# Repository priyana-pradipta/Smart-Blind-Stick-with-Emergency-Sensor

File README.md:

# Smart-Blind-Stick-with-Emergency-Sensor
Embedded Systems Course Final Project

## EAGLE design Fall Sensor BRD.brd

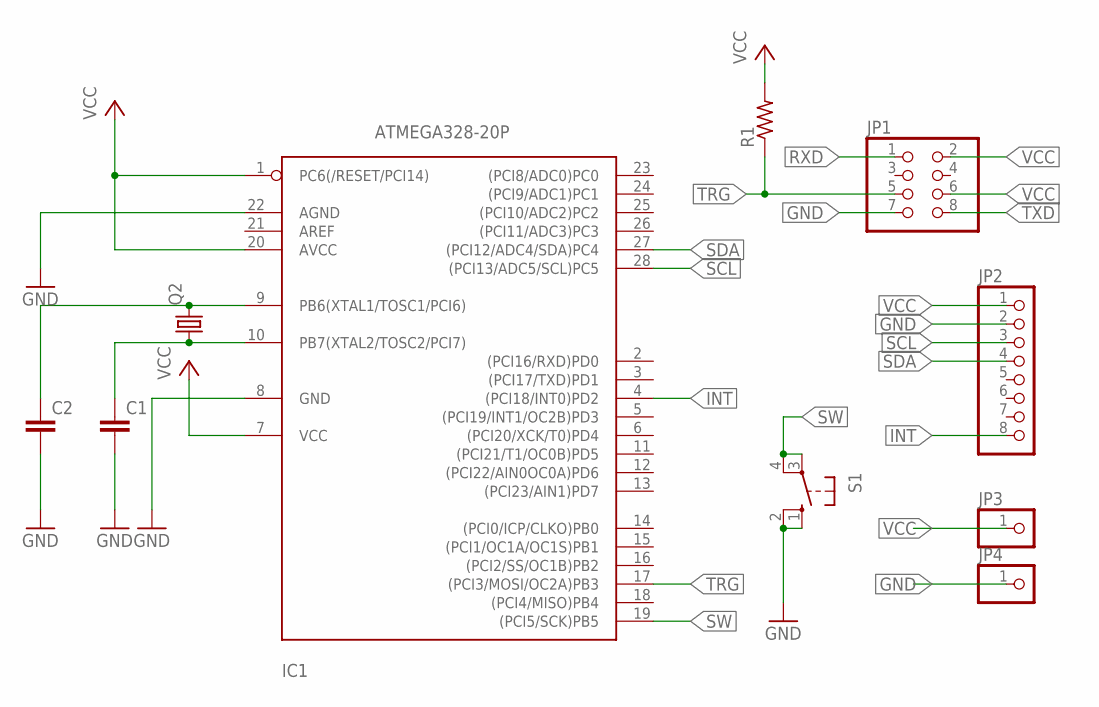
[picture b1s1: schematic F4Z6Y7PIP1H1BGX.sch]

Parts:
C1, C2: C2,5-3; C2.5-3
IC1: ATMEGA328-20P; DIL28-3
JP1: PINHD-2X4; 2X04
JP2: PINHD-1X8/90; 1X08/90
JP3, JP4: PINHD-1X1; 1X01
Q2: CRYSTALHC49S; HC49/S
R1: R-US_0204/7; 0204/7
S1: 10-XX; B3F-10XX

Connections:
GND: C1.2, C2.2, IC1.8 (GND), IC1.22 (AGND), JP1.7, JP2.2, JP4.1, S1.1 (S), S1.2 (S1)
INT: IC1.4 ((PCI18/INT0)PD2), JP2.8
unnamed: C2.1, IC1.9 (PB6(XTAL1/TOSC1/PCI6)), Q2.2
unnamed: C1.1, IC1.10 (PB7(XTAL2/TOSC2/PCI7)), Q2.1
RXD: JP1.1
SCL: IC1.28 ((PCI13/ADC5/SCL)PC5), JP2.3
SDA: IC1.27 ((PCI12/ADC4/SDA)PC4), JP2.4
SW: IC1.19 ((PCI5/SCK)PB5), S1.3, S1.4 (P1)
TRG: IC1.17 ((PCI3/MOSI/OC2A)PB3), JP1.5, R1.1
TXD: JP1.8
VCC: IC1.1 (PC6(/RESET/PCI14)), IC1.7 (VCC), IC1.20 (AVCC), JP1.2, JP1.6, JP2.1, JP3.1, R1.2

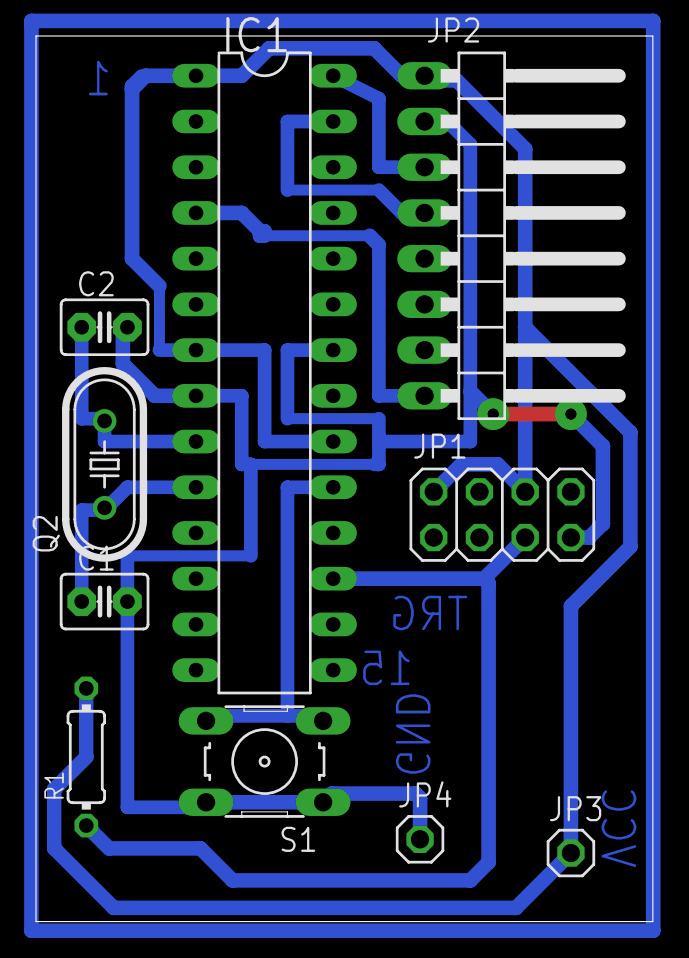
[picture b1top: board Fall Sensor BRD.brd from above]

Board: 2 copper layers, 34.3 x 49.2 mm, 10 parts (0 on the bottom side), 9 nets.
